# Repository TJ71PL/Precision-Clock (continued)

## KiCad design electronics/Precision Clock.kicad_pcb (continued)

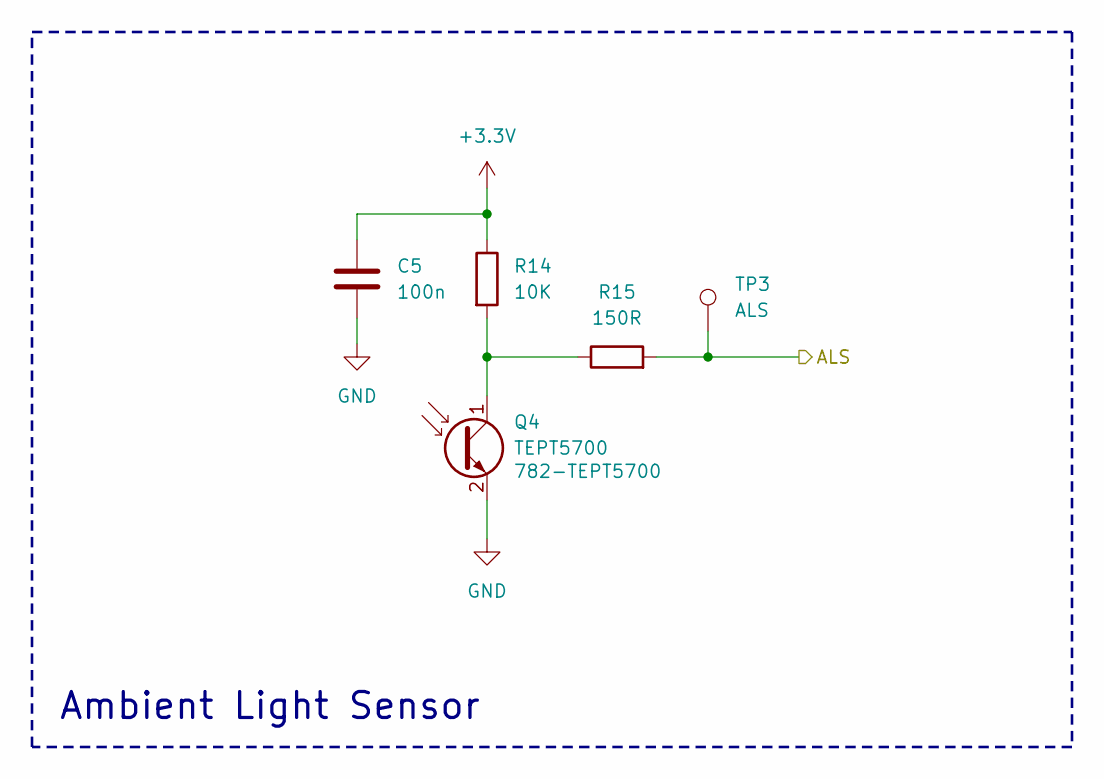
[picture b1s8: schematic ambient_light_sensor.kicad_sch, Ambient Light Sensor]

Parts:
C5: 100n; C_0402_1005Metric; LCSC C1525
Q4: TEPT5700; LED_D5.0mm_Clear; Mouser 782-TEPT5700
R14: 10K; R_0402_1005Metric; LCSC C60489
R15: 150R; R_0402_1005Metric; LCSC C276273
TP3: ALS; TestPoint_Pad_D1.0mm

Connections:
+3.3V: C5.1, R14.1; also elsewhere on the board
/Ambient Light Sensor/ALS: R15.2, TP3.1; also elsewhere on the board
GND: C5.2, Q4.2 (E); also elsewhere on the board
unnamed: Q4.1 (C), R14.2, R15.1

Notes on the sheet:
Ambient Light Sensor

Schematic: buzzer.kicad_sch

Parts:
C24: 100n; C_0402_1005Metric; LCSC C1525
LS1: PS1740P02CE; TDK PS1740P02CE; Mouser 810-PS1740P02CE
Q3: DMN3008SFG; Diodes_PowerDI3333-8; LCSC C384563
R28, R33, R37: 330R; R_0402_1005Metric; LCSC C276273
R29: 150R; R_0402_1005Metric; LCSC C276273
R32: 10K; R_0402_1005Metric; LCSC C60489
TP4: BZ; TestPoint_Pad_D1.0mm

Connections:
+3.3V: C24.1, LS1.1, R28.1; also elsewhere on the board
/Buzzer/BZ: R29.1, TP4.1; also elsewhere on the board
GND: C24.2, Q3.1 (S), Q3.2 (S), Q3.3 (S), R32.2; also elsewhere on the board
unnamed: LS1.2, Q3.5 (D), R37.2
unnamed: Q3.4 (G), R29.2, R32.1
unnamed: R28.2, R33.1
unnamed: R33.2, R37.1

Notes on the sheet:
Buzzer

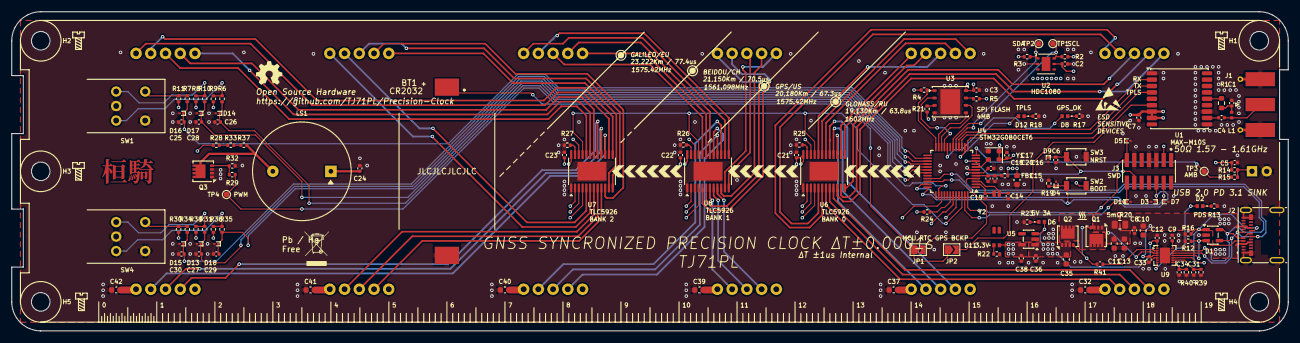
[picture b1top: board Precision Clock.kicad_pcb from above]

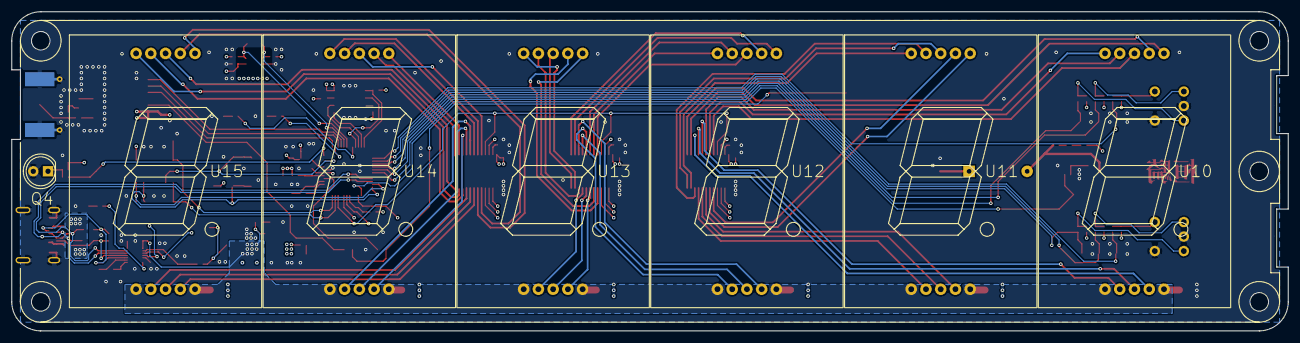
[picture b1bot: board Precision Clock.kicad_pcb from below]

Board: 4 copper layers, 220.0 x 55.0 mm, 144 parts (7 on the bottom side), 128 nets.

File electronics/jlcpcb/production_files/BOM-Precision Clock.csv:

Comment,Designator,Footprint,LCSC,Quantity
100K,R40,R_0402_1005Metric,C60491,1
100n,"C12,C17,C18,C2,C20,C21,C22,C23,C24,C3,C33,C5,C6,C7,C8",C_0402_1005Metric,C1525,15
10K,"R10,R11,R14,R19,R30,R31,R32,R34,R35,R36,R38,R6,R7,R8,R9",R_0402_1005Metric,C60489,15
10R,R1,R_0603_1608Metric,C109318,1
10n,"C1,C25,C26,C27,C28,C29,C30,C31,C34",C_0402_1005Metric,C15195,9
10u,"C10,C11,C13,C32,C35,C37,C39,C40,C41,C42",C_0603_1608Metric,C86275,10
12.5p,"C14,C19",C_0402_1005Metric,C26406,2
120R@100MHz,FB1,R_0402_1005Metric,C38480,1
150R,"R15,R17,R18,R22,R29",R_0402_1005Metric,C138054,5
1u,"C16,C36,C38,C9",C_0402_1005Metric,C29266,4
22R,R24,R_0402_1005Metric,C114765,1
27nH 5%,L1,L_0402_1005Metric,C12669,1
330R,"R13,R23,R28,R33,R37",R_0402_1005Metric,C105875,5
39K,R39,R_0402_1005Metric,C137995,1
4.7u,C15,C_0603_1608Metric,C69335,1
47pF,C4,C_0402_1005Metric,C437519,1
5.1K,"R12,R16,R2,R21,R3,R4,R41,R5",R_0402_1005Metric,C105872,8
5mR,R20,R_0805_2012Metric,C92742,1
750R,"R25,R26,R27",R_0402_1005Metric,C137936,3
AP2127K-3.3,U5,SOT-23-5,C156285,1
AP33771C,U9,W-DFN3030-14 (Type A1) Diodes,C24735840,1
B3U-1000P,"SW2,SW3",SW_SPST_B3U-1000P,C231329,2
CR2032,BT1,Battery_holder_CR2032_SMD,C70377,1
Conn_ST_STDC14,J3,ST STDC14,C7465995,1
DMN3008SFG,"Q1,Q2,Q3",Diodes_PowerDI3333-8,C384563,3
ECS-TXO-2520MV,Y1,ECS_TXO-2520MV,C2602138,1
ESDA6V1SC5,D1,SOT-23-5,C2935146,1
ESDALC6V1-1U2,"D10,D13,D14,D15,D16,D17,D18,D3,D4,D5,D7,D9",ST ESDALC6V1-1U2,C1974498,12
HDC1080,U2,Texas_PWSON-N6,C82227,1
LED,D8,LED_LiteON_LTST-C281KGKT,C160479,1
LED,"D11,D12,D2,D6",LED_LiteON_LTST-C281KGKT,C364556,4
Q13MC14620002,Y2,Crystal_SMD_SeikoEpson_MC146-4Pin_6.7x1.5mm,C15482,1
STM32G0B0CET6,U4,LQFP-48_7x7mm_P0.5mm,C2826978,1
TLC5926,"U6,U7,U8",HTSSOP-24-1EP_4.4x7.8mm_P0.65mm_EP3.2x5mm,C527434,3
USB_C_Receptacle,J2,USB_C_Receptacle_Molex_105450-0101,C134092,1
W25Q32JVZP,U3,WSON-8-1EP_6x5mm_P1.27mm_EP3.4x4.3mm,C571260,1

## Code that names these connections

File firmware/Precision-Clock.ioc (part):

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Mcu.Name=STM32G0B0CETx
Mcu.Package=LQFP48
Mcu.UserName=STM32G0B0CETx
PA13.Mode=Serial_Wire
PA13.Signal=SYS_SWDIO
PA14-BOOT0.Mode=Serial_Wire
PA14-BOOT0.Signal=SYS_SWCLK
PB3.GPIOParameters=GPIO_Speed,PinState,GPIO_Label
PB3.GPIO_Label=DISPLAY_CLK
PB3.GPIO_Speed=GPIO_SPEED_FREQ_VERY_HIGH
PB3.Mode=TX_Only_Simplex_Unidirect_Master
PB3.PinState=GPIO_PIN_RESET
PB3.Signal=SPI1_SCK
PB5.GPIOParameters=GPIO_Speed,PinState,GPIO_Label
PB5.GPIO_Label=DISPLAY_DATA
PB5.GPIO_Speed=GPIO_SPEED_FREQ_VERY_HIGH
PB5.Mode=TX_Only_Simplex_Unidirect_Master
PB5.PinState=GPIO_PIN_RESET
PB5.Signal=SPI1_MOSI
PB7.GPIOParameters=GPIO_Speed,GPIO_Label
PB7.GPIO_Label=DISPLAY_BRIGHTNESS
PB7.GPIO_Speed=GPIO_SPEED_FREQ_HIGH
PB7.Signal=S_TIM4_CH2
PC14-OSC32_IN\ (PC14).Mode=LSE-External-Oscillator
PC14-OSC32_IN\ (PC14).Signal=RCC_OSC32_IN
PC15-OSC32_OUT\ (PC15).Mode=LSE-External-Oscillator
PC15-OSC32_OUT\ (PC15).Signal=RCC_OSC32_OUT
PD0.GPIOParameters=GPIO_Label
PD0.GPIO_Label=BUZZER
PD0.Signal=S_TIM16_CH1
PD1.GPIOParameters=GPIO_Speed,GPIO_PuPd,GPIO_Label
PD1.GPIO_Label=DISPLAY_UPDATE
PD1.GPIO_PuPd=GPIO_PULLDOWN
PD1.GPIO_Speed=GPIO_SPEED_FREQ_HIGH
PD1.Signal=GPIO_Output
PF0-OSC_IN\ (PF0).Mode=HSE-External-Clock-Source
PF0-OSC_IN\ (PF0).Signal=RCC_OSC_IN
RCC.HSE_VALUE=10000000
RCC.SYSCLKFreq_VALUE=60000000
RCC.SYSCLKSource=RCC_SYSCLKSOURCE_PLLCLK
board=custom

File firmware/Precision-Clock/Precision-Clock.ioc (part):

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Mcu.Name=STM32G0B0CETx
Mcu.Package=LQFP48
Mcu.UserName=STM32G0B0CETx
PA13.Mode=Serial_Wire
PA13.Signal=SYS_SWDIO
PA14-BOOT0.Mode=Serial_Wire
PA14-BOOT0.Signal=SYS_SWCLK
PA6.Mode=I2C
PA6.Signal=I2C2_SDA
PA7.Mode=I2C
PA7.Signal=I2C2_SCL
PC14-OSC32_IN\ (PC14).Mode=LSE-External-Oscillator
PC14-OSC32_IN\ (PC14).Signal=RCC_OSC32_IN
PC15-OSC32_OUT\ (PC15).Mode=LSE-External-Oscillator
PC15-OSC32_OUT\ (PC15).Signal=RCC_OSC32_OUT
PF0-OSC_IN\ (PF0).Mode=HSE-External-Clock-Source
PF0-OSC_IN\ (PF0).Signal=RCC_OSC_IN
RCC.HSE_VALUE=10000000
RCC.SYSCLKFreq_VALUE=10000000
RCC.SYSCLKSource=RCC_SYSCLKSOURCE_HSE
board=custom

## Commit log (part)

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2025-10-10 Init
2025-10-12 - addition of sensors - addition of GPS - inprogress power circuitary
2025-10-13 Restructuring of the schematic - 4 character and LED colon addition. - Ambient light sensor addition. - Sheet pin sync.
2025-10-15 change in display module
    - Created new sheets
    - Reordered the sheets
    - Created the footprint for the display
    - 3D model of the display
    - MCU selection
2025-10-16 change in display module
    - changes the display to a common anode type display
2025-10-17 primary MCU changes
    - added preliminary decoupling
    - added LSE
    - added flash memory
2025-10-19 TXCO MCU updates - change in MCU series from L5 to U5. - primary microcontroller pin out defined. - TXCO finalized. - secondary microcontroller pin out defined. - audio amplifier added.
2025-10-20 minor changes
    - removed the power, ambient light sensing circuits.
    - minor changes in the primary MCU pinout.
    - USB connector moved to MCU sheet.
    - ESD protection added.
    - removed the test points from the individual sheets.
    - Improved readability.
2025-10-22 current limit resistors
    - styling changes in the schematics
2025-10-22 minor changes
    - removal of colon LEDs
    - removal of test points addition of solders bridges
    - time pulse LED added
    - modification in MCU pinout
2025-10-22 minor changes
    - annotations added
2025-10-23 power circuit added
    - addition of power circuit
    - added bypassing circuit
    - new formatting of the schematic
    - root schematic updated
2025-10-24 addition of bus
    - cleaned up the structure of the schematic.
    - addition of the colon
    - root schematic improvements
2025-10-24 lock removal
2025-10-30 current limiting resistor changes
    - added colon led model, but might replace it in the future.
    - reduction in current limiting resistance.
    - removed the solder jumps in the individual circuit schematics.
2025-10-31 voltage regulation changes
    - ambient light sensor addition
    - colon control
    - brightness control through regulators
    - added test points
    - MCU pinout changes
2025-10-31 buzzer addition
    - reordering
    - test point addition
    - ferrite beads on both the MCUs
2025-11-03 Buzzer driver added - replacement of photoresistor to a variable resistor - added button - general formatting
2025-11-04 ESD, LEDs, footprints
    - assignment of footprints
    - ESD protection
    - User buttons
    - addition of test points
    - BOM consolidation of resistors
    - general reordering of the schematic
2025-11-05 verification
    - sensor schematic verification
    - change in the value of current limiting resistor
    - disconnected unused buffer pins
    - labeling or peripherals used in primary MCU
    - additional user button
    - DRC corrections
2025-11-07 semi final verification
    - change in display type to common cathode
    - verification of the schematic
    - addition of footprints
    - further minor changes
2025-11-10 PCB routing
    - JLCPCB constraints added
    - removal of multiple test points
    - change of footprints
    - change of THT LEDs
    - rough position of all the major components
    - PCB routing started
2025-11-11 PCB routing
    - addition of 3D models
    - addition of docs
    - reduction of the size of passives
    - increase in size of traces
2025-11-12 PCB routing
2025-11-13 PCB routing restarted
    - removal of all previous traces and vias
    - placement of most of the parts
    - priority towards high speed lines like USB and USART
2025-11-14 PCB routing
    - high priority nets connected
    - primary MCU nets connected
    - reposition of footprints
2025-11-17 PCB routing
    - secondary MCU routing started
    - primary MCU routing completed
2025-11-18 PCB routing
    - low power trace routing completion
2025-11-21 Major overhaul required
    - Secondary MCU External clock to be included
    - possible removal of colon drivers
    - priority towards the end product over schematic
    - high speed signals to be tuned like QSPI and USB
2025-11-25 Primary MCU rerouting
2025-11-26 Secondary MCU rerouting
2025-11-27 Secondary MCU rerouting
    - Bank 2 completion
    - OSC net completion
2025-11-28 Secondary MCU complete
2025-12-01 Position correction
2025-12-02 High power routing
2025-12-23 Schematic changes
    - signal for dots are removed.
    - power supply upgraded to buck converters.
    - individually addressable Colon LEDs.
    - second millisecond dot separator signal is not connected.
    - buzzer can now be connected to PWM or DAC outputs.
2025-12-24 Power stage changes
    - removal of potentiometer
    - addition of rotary encoder
    - addition of ambient light sensor
    - addition of unity gain differential amplifier.
    - reording of the schematic.
2026-01-23 updated power
2026-01-25 Restructuring
2026-01-26 Pin out completion
2026-01-26 Removal of Colon LEDs
2026-01-26 buzzer and ambient light sensor added
2026-01-27 removal of sensors
2026-01-27 addition of BME690
2026-01-28 Changed BOOT0 switch
2026-01-29 Removed One Rotary Encoder
2026-01-29 Verification
    - changed the piezo electric speaker.
    - verified some schematics
2026-02-02 Power subsystem updated
2026-02-04 Verification
2026-02-05 display driver update
2026-02-06 Display Driver Completion
2026-02-09 Footprints added
2026-02-24 Major Changes
2026-02-26 Encoder placement
2026-02-26 TJ71PL added
2026-02-27 Minor changes
2026-02-28 Production files preparation
2026-03-08 In Production
2026-03-10 Footprint Fix Production Paused
2026-03-11 Push Button Replacement
2026-03-12 MCU replacement
2026-03-12 Routing
2026-03-14 Production Ready v2
2026-03-15 firmware init
2026-06-09 Firmware Dev Init
2026-06-10 counter
